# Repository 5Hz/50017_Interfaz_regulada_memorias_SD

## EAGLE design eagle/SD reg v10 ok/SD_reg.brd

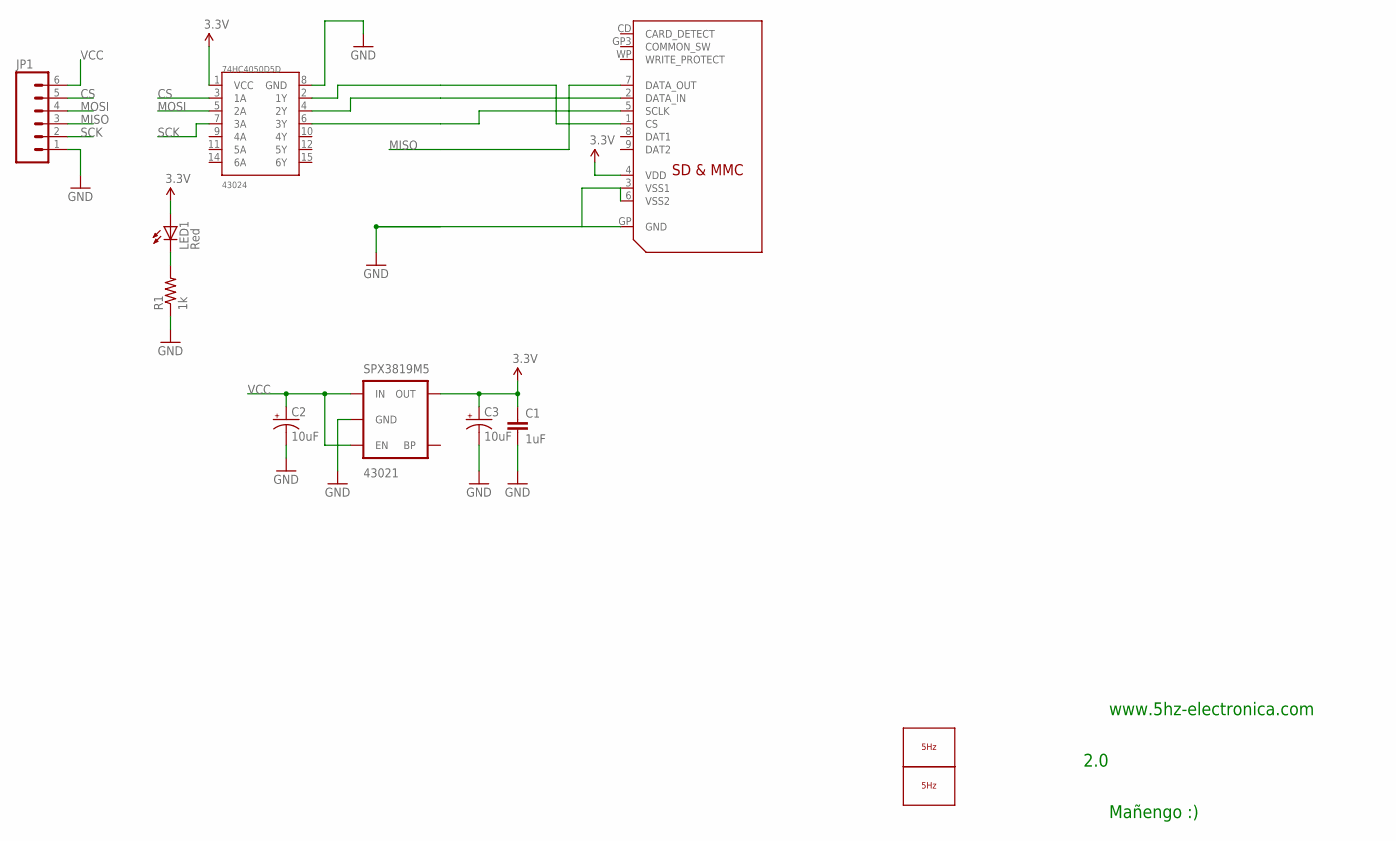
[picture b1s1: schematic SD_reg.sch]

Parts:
74HC4050D5D: 43024; SO016
C1: 1uF; 0603-CAP
C2, C3: 10uF; EIA3216
JP1: M06SIP; 1X06
LED1: Red; LED-0603
LOGO1: LOGO_5HZ_MAIN_10MM; 5HZ_LOGO_MAIN_10MM
LOGO2: LOGO_5HZ_CIRC_3MM; 5HZ_LOGO_CIRC_3MM
R1: 1k; 0603-RES
SPX3819M5: 43021; SOT23-5
U$1: 2041021-4; 06132

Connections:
3.3V: 74HC4050D5D.1 (VCC), C1.1, C3.A (+), LED1.A, SPX3819M5.5 (OUT), U$1.4 (VDD)
CS: 74HC4050D5D.3 (1A), JP1.5
GND: 74HC4050D5D.8 (GND), C1.2, C2.C (-), C3.C (-), JP1.1, R1.1, SPX3819M5.2 (GND)
MISO: JP1.3, U$1.7 (DATA_OUT)
MOSI: 74HC4050D5D.5 (2A), JP1.4
unnamed: 74HC4050D5D.4 (2Y), U$1.2 (DATA_IN)
unnamed: 74HC4050D5D.6 (3Y), U$1.5 (SCLK)
unnamed: LED1.C, R1.2
unnamed: 74HC4050D5D.2 (1Y), U$1.1 (CS)
SCK: 74HC4050D5D.7 (3A), JP1.2
VCC: C2.A (+), JP1.6, SPX3819M5.1 (IN), SPX3819M5.3 (EN)
VSS2: U$1.3 (VSS1), U$1.6 (VSS2), U$1.GP (GND)

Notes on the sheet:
www.5hz-electronica.com
Mañengo :)
2.0

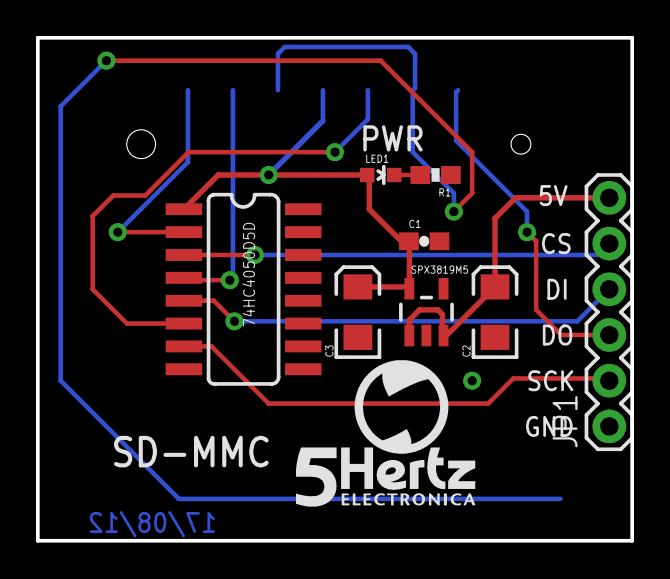
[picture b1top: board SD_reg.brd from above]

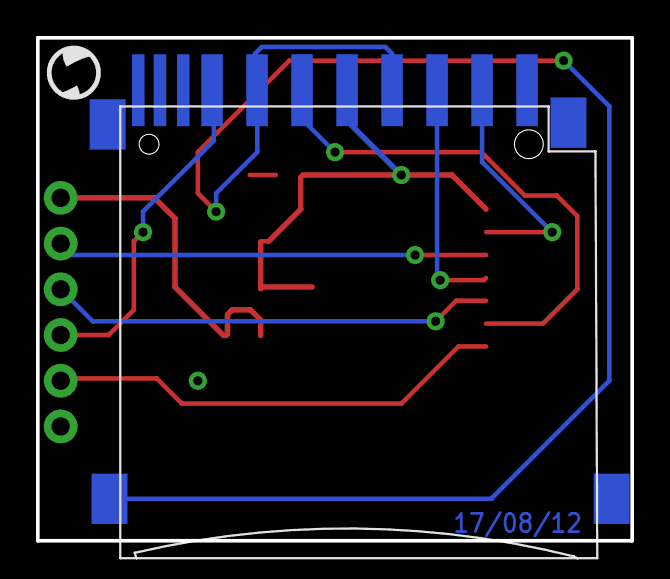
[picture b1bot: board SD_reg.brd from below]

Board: 2 copper layers, 33.0 x 27.9 mm, 11 parts (2 on the bottom side), 12 nets.

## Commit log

2014-01-15 Creacion
